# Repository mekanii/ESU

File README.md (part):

# 1. General Concept

# 2. Component
## 2.1. Monopolar Switch Detection (MSD)
### 2.1.1. Schematic

### 2.1.2. Output Scope
- Cut
- Coag

## 2.2. Return Electrode Monitor (REM)
### 2.2.1. Schematic

### 2.2.2. Output Scope
#### 2.2.2.1. Transformer
Below is the output scope at the input and output of toroidal transformer.

#### 2.2.2.2 Sense
> [!NOTE]
> All measurements for Return Electrode Monitoring do not utilize a physical Return Electrode; instead, a variable resistor is used. Therefore, all references to **pad resistance** in this context describe the variable resistor that simulates the Return Electrode.

Below is the output scope from the sense circuit, where the pad resistance values are 5Ω, 200Ω, 1kΩ, and High Impedance. The voltages measured by the oscilloscope are 10.385 mV, 558.91 mV, 689.31 mV, and 1.1164 V, respectively.

The ESP32's ADC provides a versatile and powerful way to read analog signals with a resolution of up to 12 bits and operates with a reference voltage of 0V to 3.3V (the default voltage range). Below is the formula to calculate the voltage per level for the ADC at 12-bit resolution.

$Voltage \ per \ Level = \frac{Voltage \ Range}{2^{Resolution}} = \frac{3.3V - 0V}{2^{12}} = \frac{3.3V}{4096} ≈ 0.00080586V ≈ 0.80586 mV$

Below is the formula to calculate the ADC value based on the voltage sense and the Voltage per Level.

$ADC \ Value = \frac{V_{sense}}{Voltage \ per \ Level}$

Using the formula above, we have the following ADC values for different pad resistances:

<div align="center">

| Pad Resistance | Measured Voltage | ADC Value |
| -------------: | ---------------: | --------: |
|             5Ω |        10.385 mV |        19 |
|           200Ω |        558.91 mV |       694 |
|            1kΩ |        689.31 mV |       855 |
|         High-Z |        1116.4 mV |      1385 |

</div>

## 2.3. Controller
### 2.3.1. PWM Generator
#### 2.3.1.1. Using the Remote Control Module (RMT) of ESP32 for Generating PWM Signals
The Remote Control Module (RMT) on the ESP32 is a versatile hardware peripheral designed primarily for sending and receiving infrared signals. However, it can also be effectively utilized to generate precise Pulse Width Modulation (PWM) signals.

#### 2.3.1.2. Key Concepts
- Duty Cycle:<br>The duty cycle of a PWM signal is the percentage of one cycle in which the signal is high (on) versus low (off). It is typically expressed as a value between 0 and 100.
- Total Period:<br>The total period of the PWM signal is the sum of the HIGH time and LOW time.

#### 2.3.1.3. Configuration
##### a. Clock Divider
The clock divider is a crucial parameter in microcontroller and digital circuit design that determines the frequency of a clock signal by dividing the input clock frequency, which is APB_CLK (80 MHz) for ESP32.

$Clock \ Divider = \frac{APB \_ CLK}{Clock \ Frequency}$

##### b. Resolution
The resolution in duty cycle is a crucial parameter in microcontroller and digital circuit design that determines the granularity of control over the PWM signal. It defines how finely the duty cycle can be adjusted, allowing for precise modulation of the output signal. In the case of the ESP32, the resolution is influenced by the clock frequency which ultimately affect the ability to achieve desired output levels.

$Resolution = \frac{Clock \ Frequency}{PWM \ Frequency}$

##### c. Combination of Clock Frequency and Resolution
The combination of clock frequency and resolution plays a vital role in determining the performance of PWM signals in microcontroller applications. The clock frequency sets the base rate at which the system operates, while the resolution defines how many discrete levels the duty cycle can be divided into. A higher clock frequency allows for faster switching and more precise timing, while a higher resolution enables finer control over the duty cycle. Together, they influence the accuracy and responsiveness of the PWM output, making it essential to balance these parameters to meet the specific requirements of the application.

<div align="center">

| Mode          | f PWM    | f Clock  | Clock Div | Resolution | 
| ------------- | -------: | -------: | --------: | ---------: |
| Pure Cut      |  400 kHz |   80 MHz |         1 |        200 |
| Blend Cut 1   |  400 kHz |   80 MHz |         1 |        200 |
| Blend Cut 2   |  400 kHz |   80 MHz |         1 |        200 |
| Coag Spray    |   25 kHz |   10 MHz |         8 |        800 |
| Coag Forced   |   20 kHz |   10 MHz |         8 |       1000 |
| Coag Standard |  400 kHz |   80 MHz |         1 |        200 |

</div>

#### 2.3.1.4. Output Scope
##### a. 400kHz
- Pattern 1
<br>The image illustrates the output scope for the Pattern 1 (Pure Cut operation) at the PWM generator. It provides a detailed view of the waveform characteristics and performance metrics associated with the Pure Cut process, highlighting the key features and behavior of the PWM signal during this operation.
<br>For discrete levels ranging from 10 to 100, demonstrates similar PWM frequency, indicating consistent performance across these duty cycle settings.

> [!NOTE]
> 400kHz PWM signal utilize a discrete resolution of 200 levels.

<!--  -->

- Pattern 2<br>
The image illustrates the output scope for the Pattern 2 (Blend Cut 1) operation at the PWM generator. It provides a detailed view of the waveform characteristics and performance metrics associated with the Blend Cut process, highlighting the key features and behavior of the PWM signal during this operation.<br>
For discrete levels ranging from 10 to 100, demonstrates similar PWM frequency and similar waveform HIGH state periods, indicating consistent performance across these duty cycle settings. Each pulse in Blend Cut 1 is similar to a single pulse of a Pattern 1 (Pure Cut) PWM signal.

> [!NOTE]
> Pattern 2: 18 pulses per 1 modulation (400 kHz for each pulse, with 0% PWM during the last 2 periods).<br>This pattern utilize a discrete resolution of 200 levels, similar to that of a Pattern 1 (Pure Cut) PWM signal.

- Pattern 3
<br>The image illustrates the output scope for the Pattern 3 (Blend Cut 2) operation at the PWM generator. It provides a detailed view of the waveform characteristics and performance metrics associated with the Blend Cut process, highlighting the key features and behavior of the PWM signal during this operation.
<br>For discrete levels ranging from 10 to 100, demonstrates similar PWM frequency and similar waveform HIGH state periods, indicating consistent performance across these duty cycle settings. Each pulse in Blend Cut 2 is similar to a single pulse of a Pure Cut PWM signal.

> [!NOTE]
> Pattern 3: 17 pulses per 1 modulation (400 kHz for each pulse, with 0% PWM during the last 3 periods).<br>This pattern utilize a discrete resolution of 200 levels, similar to that of a Pattern 1 (Pure Cut) PWM signal.

<!--  -->

##### b. 25kHz
The image illustrates the output scope for the 25kHz (Spray Coagulation operation) at the PWM generator. It provides a detailed view of the waveform characteristics and performance metrics associated with the Spray Coagulation process, highlighting the key features and behavior of the PWM signal during this operation.

For discrete levels ranging from 10 to 100, demonstrates similar PWM frequency, indicating consistent performance across these duty cycle settings. We can observe that the increment of the duty cycle results in a pulse that exhibits a linear increase in HIGH time, further emphasizing the effectiveness of the PWM modulation in maintaining a predictable response across varying duty cycle levels.

> [!NOTE]
> 25kHz PWM signal utilize a discrete resolution of 800 levels.

<p align="center">

</p>

<div align="center">

| Discrete Level  | Duty Cycle  | HIGH Time | LOW Time  |
| ---------------:| -----------:| ---------:| ---------:|
|              10 |      1.25 % |    0.5 µs |   39.5 µs |
|              20 |      2.50 % |    1.0 µs |   39.0 µs |
|              30 |      3.75 % |    1.5 µs |   38.5 µs |
|              40 |      5.00 % |    2.0 µs |   38.0 µs |
|              50 |      6.25 % |    2.5 µs |   37.5 µs |
|              60 |      7.50 % |    3.0 µs |   37.0 µs |
|              70 |      8.75 % |    3.5 µs |   36.5 µs |
|              80 |     10.00 % |    4.0 µs |   36.0 µs |
|              90 |     11.25 % |    4.5 µs |   35.5 µs |
|             100 |     12.50 % |    5.0 µs |   35.0 µs |

</div>

##### c. 20kHz
The image illustrates the output scope for the 20kHz (Forced Coagulation operation) at the PWM generator. It provides a detailed view of the waveform characteristics and performance metrics associated with the Forced Coagulation process, highlighting the key features and behavior of the PWM signal during this operation.

For discrete levels ranging from 10 to 100, demonstrates similar PWM frequency, indicating consistent performance across these duty cycle settings. We can observe that the increment of the duty cycle results in a pulse that exhibits a linear increase in HIGH time, further emphasizing the effectiveness of the PWM modulation in maintaining a predictable response across varying duty cycle levels.

> [!NOTE]
> 20kHz PWM signal utilize a discrete resolution of 1000 levels.

<p align="center">

</p>

<div align="center">

| Discrete Level  | Duty Cycle  | HIGH Time | LOW Time  |
| ---------------:| -----------:| ---------:| ---------:|
|              10 |      1.00 % |    0.5 µs |   49.5 µs |
|              20 |      2.00 % |    1.0 µs |   49.0 µs |
|              30 |      3.00 % |    1.5 µs |   48.5 µs |
|              40 |      4.00 % |    2.0 µs |   48.0 µs |
|              50 |      5.00 % |    2.5 µs |   47.5 µs |
|              60 |      6.00 % |    3.0 µs |   47.0 µs |
|              70 |      7.00 % |    3.5 µs |   46.5 µs |
|              80 |      8.00 % |    4.0 µs |   46.0 µs |
|              90 |      9.00 % |    4.5 µs |   45.5 µs |
|             100 |     10.00 % |    5.0 µs |   45.0 µs |

</div>

### 2.3.2. Communication Protocol
<!-- 0x5000-0x7FFF can be used as the variable address range; 0x8000-0xFFFF -->
The system UART mode is fixed to 8N1, and the baud rate is 115200.

**Frame Structure**

The data frame consists of 5 data blocks:

```[HEADER] [LENGTH] [INSTRUCTION] [PAYLOAD] [CRC]```

**Frame Components**

<table>
  <thead>
    <tr>
      <td>Block</td>
      <td>Size [byte]</td>
      <td>Description</td>
      <td>Value</td>
    </tr>
  </thead>
  <tbody>
    <tr>
      <td>HEADER</td>
      <td>2</td>
      <td>Frame start marker</td>
      <td>0x5A 0XA5</td>
    </tr>
    <tr>
      <td>LENGTH</td>
      <td>1</td>
      <td>Total bytes after HEADER</td>
      <td>INSTRUCTION + DATA + CRC</td>
    </tr>
    <tr>
      <td>INSTRUCTION</td>
      <td>1</td>
      <td>Instruction Code</td>
      <td>0x82 : Write<br>0x83 : Read</td>
    </tr>
    <tr>
      <td>PAYLOAD</td>
      <td>0 - 3</td>
      <td>Payload data</td>
      <td></td>
    </tr>
    <tr>
      <td>CRC</td>
      <td>2</td>
      <td>Cyclic Redundancy Check</td>
      <td></td>
    </tr>
  </tbody>
</table>

The `PAYLOAD` frame consist 3 data blocks:

```[VP ADDRESS] [NUMBER OF WORDS] [DATA]```

<table>
  <thead>
    <tr>
      <td>Block</td>
      <td>Size [byte]</td>
      <td>Description</td>
    </tr>
  </thead>
  <tbody>
    <tr>
      <td>VP ADDRESS</td>
      <td>2</td>
      <td>Variable Pointer address to read from</td>
    </tr>
    <tr>
      <td>NUMBER OF WORDS</td>
      <td>1</td>
      <td>Number of data words to read (always 1)</td>
    </tr>
    <tr>
      <td>DATA</td>
      <td>2</td>
      <td>Data word read from the specified VP address</td>
    </tr>
  </tbody>
</table>

#### 2.3.2.1. Basic System Operations

<table>
  <thead>
    <tr>
      <td nowrap>Command</td>
      <td nowrap>Variable</td>
      <td nowrap>VP ADDRESS</td>
      <td>INSTRUCTION</td>
      <td nowrap>Data Frame</td>
      <td nowrap>Response</td>
    </tr>
  </thead>
  <tbody>
    <tr></tr>
    <tr>
      <td nowrap>System status query</td>
      <td><pre>(byte) vp_50[0]</pre></td>
      <td><pre>50 00</pre></td>
      <td><pre>83</pre></td>
      <td><pre>5A A5 08 [INSTRUCTION] 50 00 01 [DATA:H DATA:L] CRC:L CRC:H</pre></td>
      <td nowrap></td>
    </tr>
    <tr></tr>
    <tr>
      <td nowrap>System reset</td>
      <td><pre>(byte) vp_50[1]</pre></td>
      <td><pre>50 01</pre></td>
      <td><pre>82</pre></td>
      <td><pre>5A A5 08 [INSTRUCTION] 50 01 01 [DATA:H DATA:L] CRC:L CRC:H</pre></td>
      <td nowrap></td>
    </tr>
    <tr></tr>
    <tr>
      <td nowrap>Stop all RMT transmission</td>
      <td><pre>(byte) vp_50[2]</pre></td>
      <td><pre>50 02</pre></td>
      <td><pre>82</pre></td>
      <td><pre>5A A5 08 [INSTRUCTION] 50 02 01 [DATA:H DATA:L] CRC:L CRC:H</pre></td>
      <td nowrap></td>
    </tr>
  </tbody>
</table>

#### 2.3.2.2. Mode Selection
<table>
  <thead>
    <tr>
      <td nowrap>Command</td>
      <td nowrap>Variable</td>
      <td nowrap>VP ADDRESS</td>
      <td>INSTRUCTION</td>
      <td nowrap>Data Frame</td>
      <td nowrap>DATA</td>
      <td nowrap>Response</td>
    </tr>
  </thead>
  <tbody>
    <tr></tr>
    <tr>
      <td nowrap>Get/set mode selection Cut</td>
      <td><pre>(int) vp_51[0]</pre></td>
      <td><pre>51 00</pre></td>
      <td><pre>82 | 83</pre></td>
      <td><pre>5A A5 08 [INSTRUCTION] 51 00 01 [DATA:H DATA:L] CRC:L CRC:H</pre></td>
      <td nowrap>
        <pre>0: 400kHz - Pattern 1
1: 400kHz - Pattern 2
2: 400kHz - Pattern 3</pre>
      </td>
      <td nowrap></td>
    </tr>
    <tr></tr>
    <tr>
      <td nowrap>Get/set mode selection Coag</td>
      <td><pre>(int) vp_51[1]</pre></td>
      <td><pre>51 01</pre></td>
      <td><pre>82 | 83</pre></td>
      <td><pre>5A A5 08 [INSTRUCTION] 51 01 01 [DATA:H DATA:L] CRC:L CRC:H</pre></td>
      <td nowrap>
        <pre>0: 25kHz
1: 20kHz
2: 400kHz - Bipolar Standard</pre>
      </td>
      <td nowrap></td>
    </tr>
  </tbody>
</table>

#### 2.3.2.2. Discrete Level Adjustment
<table>
  <thead>
    <tr>
      <td nowrap>Command</td>
      <td nowrap>Variable</td>
      <td nowrap>VP ADDRESS</td>
      <td>INSTRUCTION</td>
      <td nowrap>Data Frame</td>
      <td nowrap>DATA</td>
      <td nowrap>Response</td>
    </tr>
  </thead>
  <tbody>
    <tr></tr>
    <tr>
      <td nowrap>Get/set discrete level 400kHz - Pattern 1</td>
      <td><pre>(int) vp_52[0]</pre></td>
      <td><pre>52 00</pre></td>
      <td><pre>82 | 83</pre></td>
      <td><pre>5A A5 08 [INSTRUCTION] 52 00 01 [DATA:H DATA:L] CRC:L CRC:H</pre></td>
      <td nowrap><pre>0 - 200</pre></td>
      <td nowrap></td>
    </tr>
    <tr></tr>
    <tr>
      <td nowrap>Get/set discrete level 400kHz - Pattern 2</td>
      <td><pre>(int) vp_52[1]</pre></td>
      <td><pre>52 01</pre></td>
      <td><pre>82 | 83</pre></td>
      <td><pre>5A A5 08 [INSTRUCTION] 52 01 01 [DATA:H DATA:L] CRC:L CRC:H</pre></td>
      <td nowrap><pre>0 - 200</pre></td>
      <td nowrap></td>
    </tr>
    <tr></tr>
    <tr>
      <td nowrap>Get/set discrete level 400kHz - Pattern 3</td>
      <td><pre>(int) vp_52[3]</pre></td>
      <td><pre>52 02</pre></td>
      <td><pre>82 | 83</pre></td>
      <td><pre>5A A5 08 [INSTRUCTION] 52 03 01 [DATA:H DATA:L] CRC:L CRC:H</pre></td>
      <td nowrap><pre>0 - 200</pre></td>
      <td nowrap></td>
    </tr>
    <tr></tr>
    <tr>
      <td nowrap>Get/set discrete level 25kHz</td>
      <td><pre>(int) vp_53[0]</pre></td>
      <td><pre>53 00</pre></td>
      <td><pre>82 | 83</pre></td>
      <td><pre>5A A5 08 [INSTRUCTION] 53 00 01 [DATA:H DATA:L] CRC:L CRC:H</pre></td>
      <td nowrap><pre>0 - 800</pre></td>
      <td nowrap></td>
    </tr>
    <tr></tr>
    <tr>
      <td nowrap>Get/set discrete level 20kHz</td>
      <td><pre>(int) vp_53[1]</pre></td>
      <td><pre>53 01</pre></td>
      <td><pre>82 | 83</pre></td>
      <td><pre>5A A5 08 [INSTRUCTION] 53 01 01 [DATA:H DATA:L] CRC:L CRC:H</pre></td>
      <td nowrap><pre>0 - 1000</pre></td>
      <td nowrap></td>
    </tr>
    <tr></tr>
    <tr>
      <td nowrap>Get/set discrete level 400kHz - Bipolar Standard</td>
      <td><pre>(int) vp_54[0]</pre></td>
      <td><pre>54 00</pre></td>
      <td><pre>82 | 83</pre></td>
      <td><pre>5A A5 08 [INSTRUCTION] 54 00 01 [DATA:H DATA:L] CRC:L CRC:H</pre></td>
      <td nowrap><pre>0 - 200</pre></td>
      <td nowrap></td>
    </tr>
    
  </tbody>
</table>

## 2.4. Power Stage
### 2.4.1. HF Switch
#### 2.4.1.1. Schematic

#### 2.4.1.2. MOSFET Driver
We use the TC4420 as our MOSFET driver due to its high-speed performance and ability to efficiently drive N-channel MOSFETs in various applications. The TC4420 provides a peak output current of up to 6A, allowing for rapid charging and discharging of the MOSFET gate capacitance. This capability minimizes switching losses and enhances overall efficiency in power management.

Operating within a supply voltage range of 4.5V to 18V, the TC4420 can effectively drive MOSFET gates at a voltage level of 12V, ensuring that the MOSFET turns on fully for optimal performance. Its fast switching speed, with propagation delays in the nanosecond range (typically 55ns), is crucial for high-frequency applications, reducing transition times and heat generation.

#### 2.4.1.3. Utilizing Three IRFPE50 MOSFETs in Parallel for Enhanced Performance and Reliability
We use three IRFPE50 MOSFETs in parallel to enhance the overall performance and reliability of our circuit. The decision to parallel these MOSFETs is driven by several key factors:
- Increased Current Handling:<br>Each IRFPE50 MOSFET has a maximum continuous drain current rating of I<sub>D</sub>=7.8A at T<sub>C</sub>=25°C and I<sub>D</sub>=4.9A at T<sub>C</sub>=100°C. By connecting three times as many of them in parallel, we effectively triple the total current handling capability. This is particularly beneficial in applications where high current loads are expected, ensuring that the circuit can handle the demands without overheating or exceeding the MOSFET's ratings.
- Improved Thermal Management:<br>Paralleling MOSFETs helps distribute the heat generated during operation across multiple devices. This reduces the thermal stress on each individual MOSFET, allowing for better thermal management. Proper heat dissipation is crucial for maintaining performance and preventing thermal runaway, especially in high-power applications.
- Lower On-Resistance:<br>The IRFPE50 has a low on-resistance (R<sub>DS(on)</sub>) of approximately 1.2Ω. When MOSFETs are paralleled, the effective on-resistance decreases, which results in lower conduction losses. This is advantageous for improving the efficiency of the circuit, as it minimizes the voltage drop across the MOSFETs when they are in the on state.
- Redundancy and Reliability:<br>Using multiple MOSFETs in parallel provides a level of redundancy. If one MOSFET were to fail, the remaining devices can continue to operate, thereby enhancing the overall reliability of the circuit. This is particularly important in critical applications where failure could lead to significant issues.

#### 2.4.1.4. Output Scope
##### a. 400kHz
The image illustrates the output scope for the 400kHz operation at:
- MOSFET Driver Output (blue)
- MOSFET Drain Pin (yellow)
- VDS=72V

It provides a detailed view of the waveform characteristics and performance metrics associated with the Pure Cut process, highlighting the key features and behavior of the HF Switch signal during this operation.
<br>For discrete levels ranging from 20 to 180, demonstrates similar Waveform frequency, indicating consistent performance across these duty cycle settings.

> [!NOTE]
> 400kHz PWM signal utilize a discrete resolution of 200 levels.

<!--  -->

##### b. 25KHz

##### c. 25KHz

### 2.4.2. Transformer
**Toroidal Ferrite Core Transformer**

A toroidal ferrite core transformer is a type of transformer that uses a ring-shaped (toroidal) core made from ferrite material. Ferrite is a ceramic compound consisting of iron oxide mixed with other metals, which provides high magnetic permeability and low electrical conductivity. This makes ferrite ideal for high-frequency transformer applications.

**Structure and Construction**
- Core Shape<br>
  The core is a closed loop (doughnut-shaped), which helps confine the magnetic flux within the core material, minimizing leakage and electromagnetic interference (EMI).
- Windings<br>
  Copper wire is wound around the toroidal core, usually with primary and secondary windings placed concentrically. The windings can be distributed evenly around the core to further reduce leakage inductance and stray fields.
- Ferrite Material<br>
  Ferrite cores are preferred for high-frequency operation (tens of kHz to several MHz) because they have low core losses at these frequencies compared to laminated iron cores.

**Key Advantages**
- High Efficiency<br>
  The closed magnetic path of the toroid reduces core losses and leakage flux, resulting in higher efficiency.
- Low Electromagnetic Interference (EMI)<br>
  The toroidal shape confines the magnetic field, reducing EMI and making these transformers suitable for sensitive electronic circuits.
- Compact Size<br>
  For a given power rating, toroidal transformers are generally smaller and lighter than their laminated counterparts.
- Quiet Operation<br>
  The core shape and material minimize audible hum and vibration.

**Power Handling**

The transformer’s power rating is determined by the product of output voltage and current, and the core must be sized to avoid saturation at maximum load.

**Skin Effect**

At high frequencies, the skin effect is a phenomenon in alternating current (AC) where the current density becomes highest at the surface of a conductor and decreases exponentially toward the center. This occurs because the alternating current generates a changing magnetic field, which in turn induces **eddy currents** within the conductor. These eddy currents oppose the main current flow more strongly at the center, forcing most of the AC current to flow near the surface. As a result, the effective cross-sectional area available for current flow is reduced, increasing the effective resistance of the wire at higher frequencies.

The depth at which the current density falls to 37% of its value at the surface.

$δ = \sqrt{ \frac{ ρ } { π • f • μ } }$

Where:
- ρ = resistivity of the conductor (Ω·m)
- μ = permeability of the conductor (H/m)
- f = frequency (Hz)

For high-frequency windings, consider using multiple thinner wires in parallel (Litz wire) to reduce skin effect losses.

The calculated diameter above is based on DC or low-frequency AC. For high-frequency applications, the effective area may be less than the physical area due to skin effect.

#### 2.4.2.1. Design and Calculation
<!-- Given:
- Input voltage<br>$V_{in} = 72 \ V$
- Output voltage<br>$V_{out} = 216 \ V$
- Switching frequency<br>$f = 400 \ kHz = 400,000 \ Hz$
- Core dimensions:
  - Inner diameter<br>$ID = 23.3 \ mm$
  - Outer diameter<br>$OD = 40.4 \ mm$
  - Height<br>$H = 15.1 \ mm$
- Maximum flux density<br>$B_{max} = 350 \ Gauss$
- Output current<br>$I_{out} = 0.5 \ A$ -->

##### a. Core Cross-Sectional Area ($A_e$)
The effective cross-sectional area of the core is calculated as:

$A_e = \frac{( OD – ID ) • H }{ 2 }$

<!-- $A_e  = \frac{( 40.4 – 23.3 ) • 15.1 }{ 2 } = 129.1 \ mm^2$ -->

This area is important for determining how much magnetic flux the core can handle without saturating.

##### b. Primary Turns ($N_p$)
The number of primary turns is determined by:

$N_p = \frac{ V_{in} • Duty \ Cycle • 10^{10} }{ 2 • f • B_{max} • A_e }$

<!-- $N_p = \frac{ 72 • 0.5 • 10^{10} }{ 2 • 400,000 • 350 • 129.1 } = \frac{ 360,000,000,000 }{ 36,149,400,000 }$

$N_p = 9.96 ≈ 10 \ turns$ -->

This ensures the core does not saturate at the maximum input voltage and duty cycle.

##### c. Volt per Turn
The voltage induced per turn is:

$Volt \ per \ turn = \frac{ V_{in} }{ N_p }$

<!-- $Volt \ per \ turn = \frac{ 72 }{ 10 } = 7.2 \ V/turn$ -->

##### d. Secondary Turns ($N_s$)
The number of secondary turns is:

$N_s = \frac{ V_{out} }{ Volt \ per \ turn }$

<!-- $N_s = \frac{ 216 }{ 7.2 } = 30 \text{ turns}$ -->

This ensures the transformer provides the correct output voltage.

##### e. Output Power and Currents ($N_s$)
$P = V_{out} • I_{out}$

<!-- $P = 216 • 0.5 = 108 \ W$ -->

$I_{in} = \frac{ P }{ V_{in} }$

<!-- $I_{in} = \frac{ 108 }{ 72 } = 1.5 \ A$ -->

These calculations confirm the input current required to deliver the desired output power.

For high-frequency applications, we need to consider:
- **Skin effect** - Current tends to flow on the surface of conductors at high frequencies
- **Current density** - Typically 1.5-3 A/mm² for transformer applications
- **Temperature rise** - Higher current density = more heat

##### f. Wire Diameter
To calculate the required wire diameter for a given current, use the formula:<br><br>
$dW = \sqrt{ \frac{ 4 • I }{ \pi • J } }$

Where:
- $dW = wire \ diameter$
- $I = current \ (A)$
- $J = current \ density \ (A/mm^2)$

<!-- Primary:
- $I_{in} = 1.5 \ A$
- $Current \ Density = 1.5 \ A/mm^2$
- $dW_p = \sqrt{ \frac{ 4 • 1.5 }{ 3.14 • 1.5 } } = \sqrt{ \frac{ 6 }{ 4.712 } } = 1.13 \ mm$

Secondary:
- $I_{out} = 0.5 \ A$
- $Current \ Density = 1.5 \ A/mm^2$
- $dW_s = \sqrt{ \frac{ 4 • 0.5 }{ 3.14 • 1.5 } } = \sqrt{ \frac{ 2 }{ 4.712 } } = 0.65 \ mm$ -->

##### g. High-Frequency Considerations
The skin depth in copper is approximately calculated by following formula:

$δ = \sqrt{ \frac{ ρ } { π • f • μ } }$

If our calculated wire diameters are larger than 2× skin depth, consider using:
1. **Litz wire** for better high-frequency performance
2. **Multiple parallel smaller wires** instead of single thick wire with individual wire diameter 2x skin depth
3. **Stranded wire** with individual strand diameter 2x skin depth

##### h. Wire Specification for High-Frequency Operation using Stranded wire
Required copper area is the net copper cross‑section needed to carry the target current without exceeding your thermal/current‑density limit. Pick $J$ based on allowed temperature rise and cooling. Typical transformer design uses $J=1.5$–$3.0$ A/mm²; choose the lower end for continuous duty, compact windings, or poor airflow; higher values may be acceptable for pulsed or well‑cooled designs.

$A_{req} = \frac{I}{J}$

Area per strand is the metallic copper area of a single strand. Use the bare copper diameter (exclude enamel). If you only have an enamelled wire gauge, subtract twice the enamel thickness to estimate bare diameter, or use datasheet bare area.

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
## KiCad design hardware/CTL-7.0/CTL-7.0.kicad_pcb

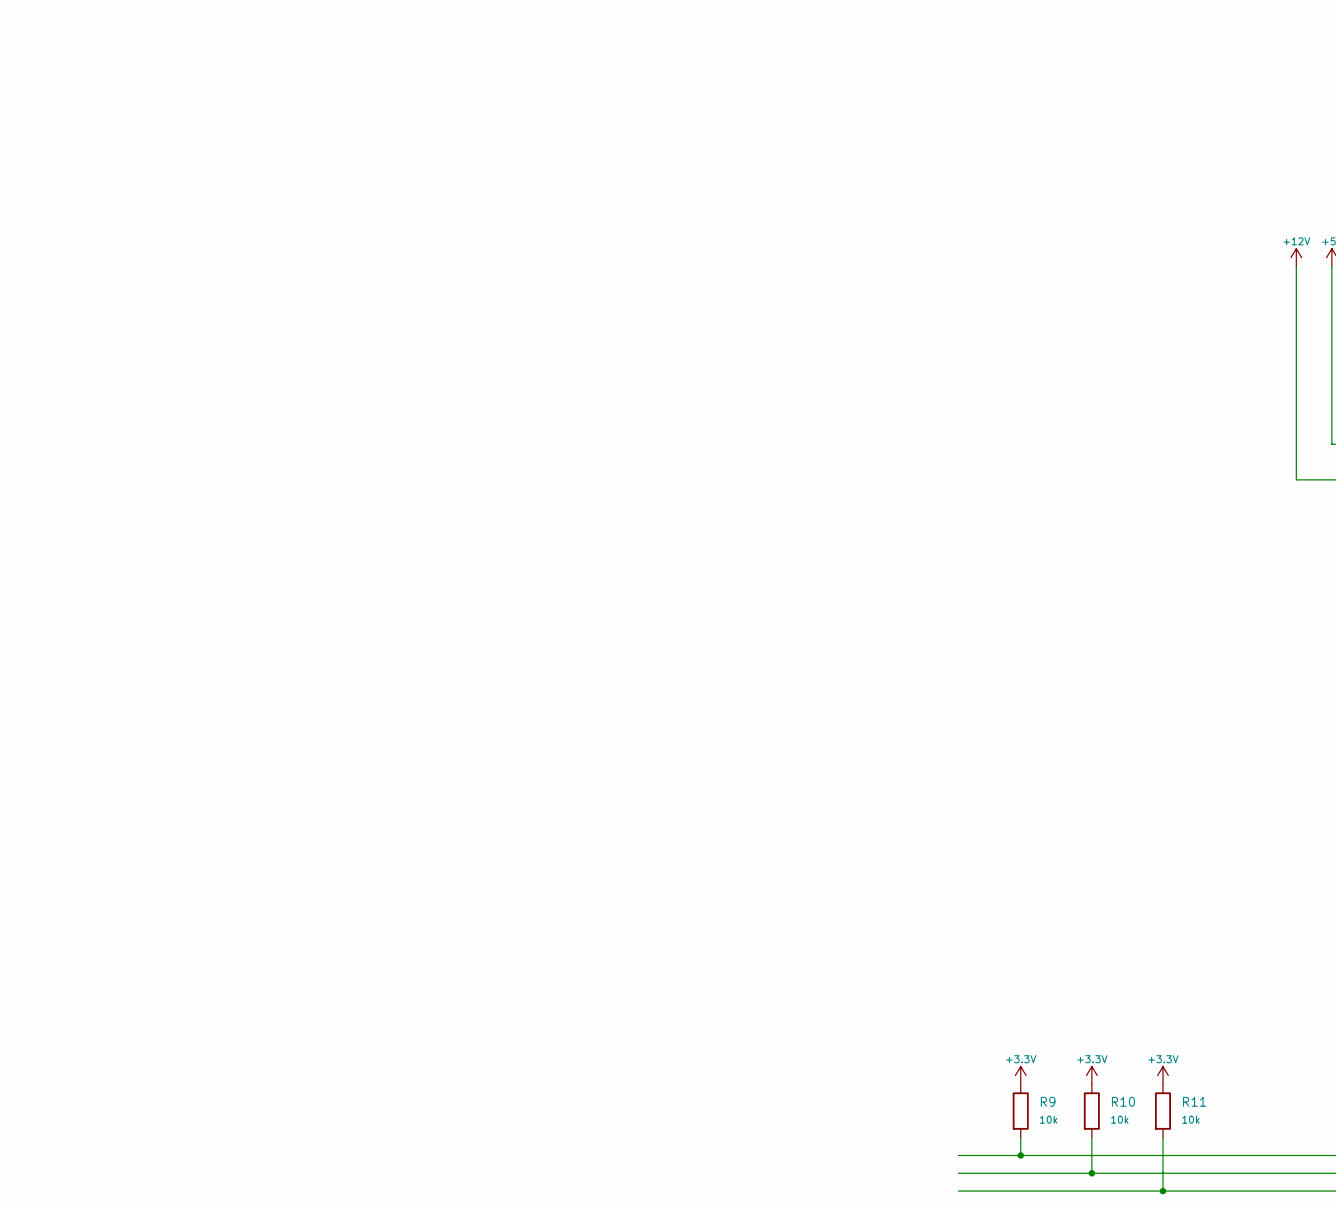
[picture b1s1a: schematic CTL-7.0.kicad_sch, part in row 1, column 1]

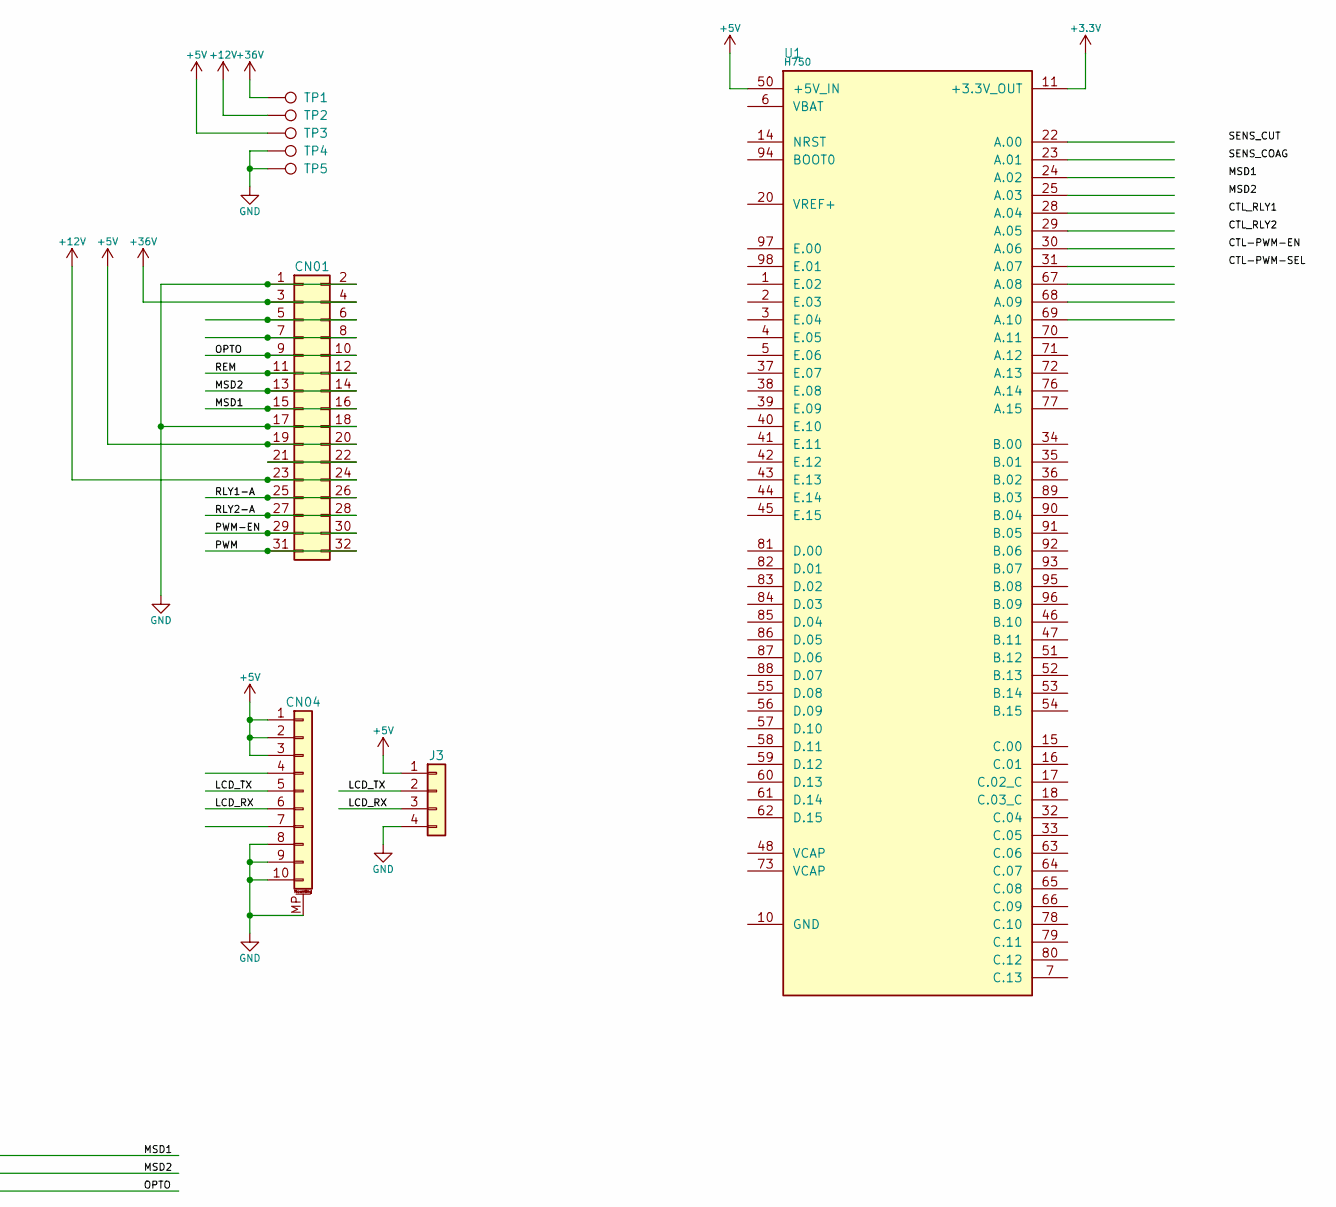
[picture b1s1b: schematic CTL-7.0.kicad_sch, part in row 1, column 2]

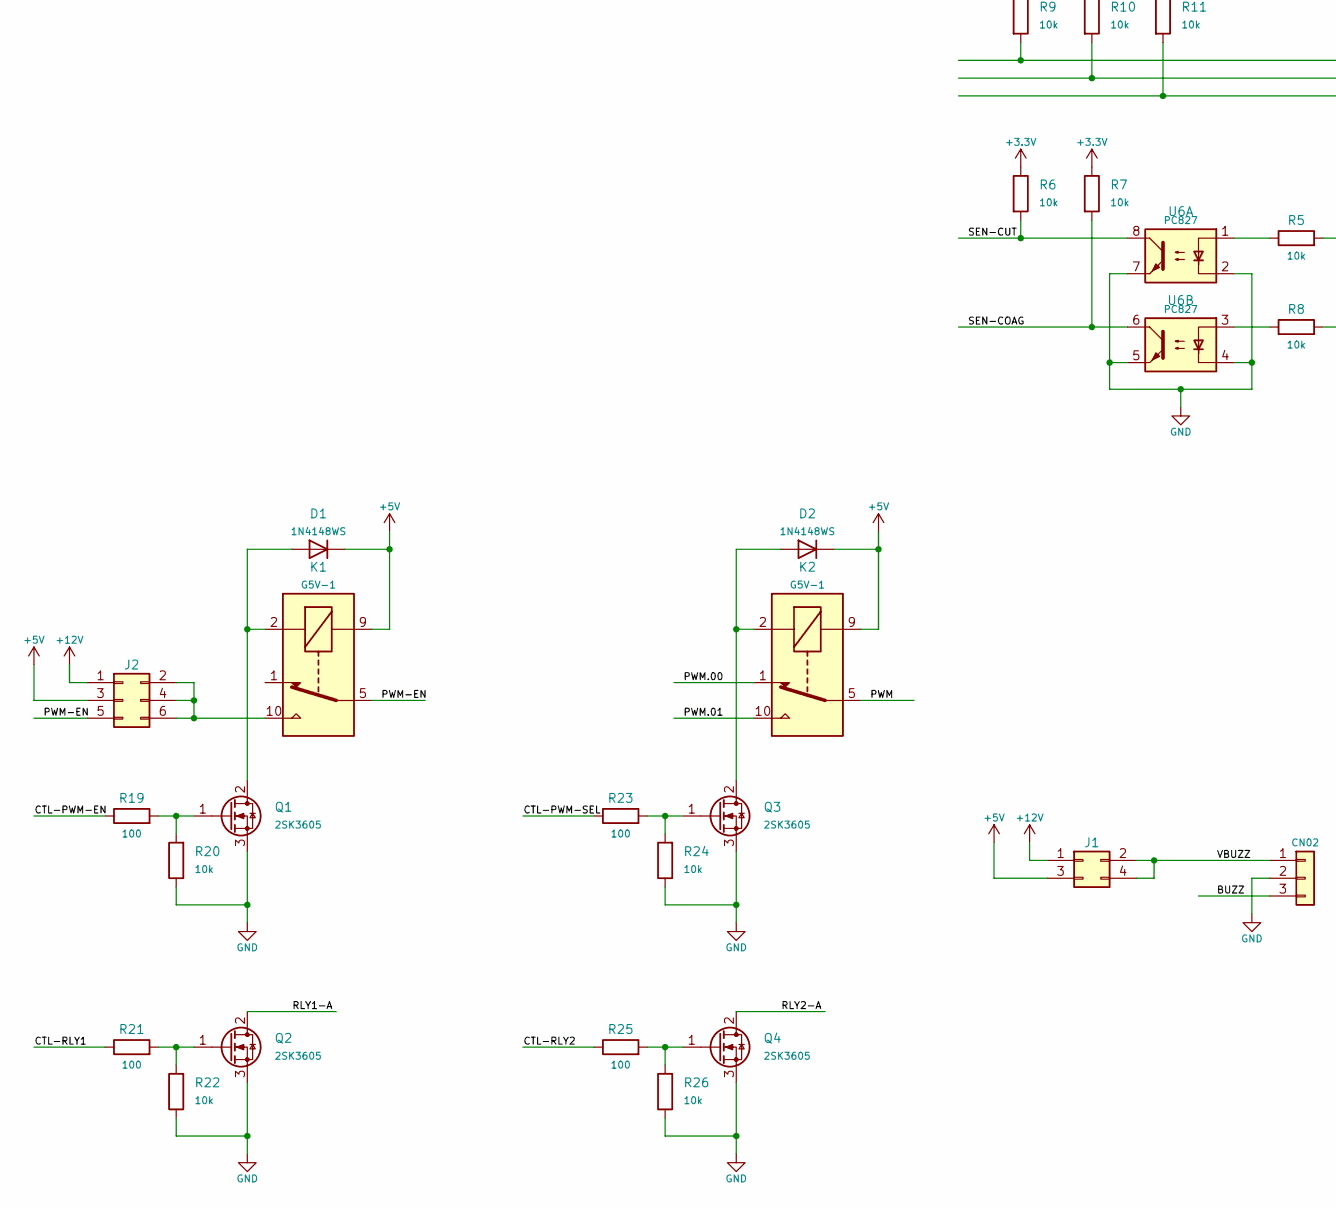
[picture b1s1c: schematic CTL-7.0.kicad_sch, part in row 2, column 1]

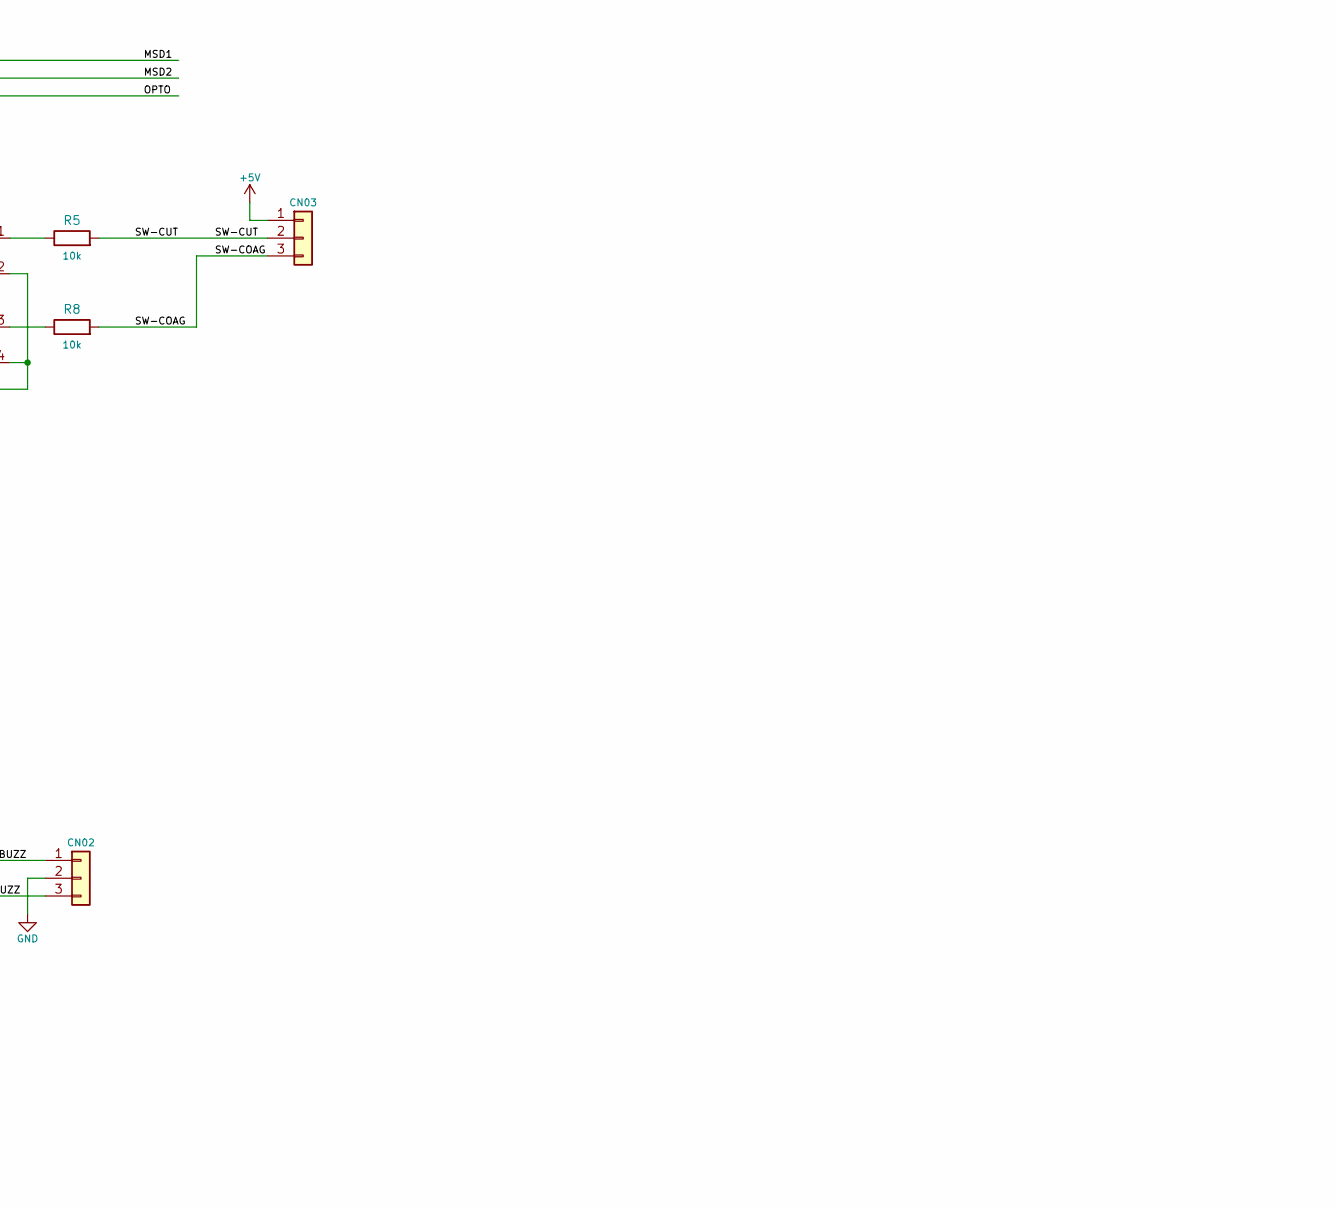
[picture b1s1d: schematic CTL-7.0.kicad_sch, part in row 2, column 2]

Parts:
CN01: Conn_02x16_Odd_Even; PinHeader_2x16_P2.54mm_Vertical
CN02, CN03: Conn_01x03; JST_XH_B3B-XH-A_1x03_P2.50mm_Vertical
CN04: TE_1-84952-0_1x10-1MP_P1.0mm_Horizontal
D1, D2: 1N4148WS; D_SOD-323
J1: Conn_02x02_Odd_Even; PinHeader_2x02_P2.54mm_Vertical_SMD
J2: Conn_02x03_Odd_Even; PinHeader_2x03_P2.54mm_Vertical_SMD
J3: Conn_01x04; PinHeader_1x04_P2.54mm_Vertical
K1, K2: G5V-1; Relay_SPDT_Omron_G5V-1
Q1, Q2, Q3, Q4: 2SK3605; SOT-89-3
R5, R6, R7, R8, R9, R10, R11, R20, R22, R24, R26: 10k; R_0805_2012Metric
R19, R21, R23, R25: 100; R_0805_2012Metric
TP1, TP2, TP3, TP4, TP5: TestPoint; TestPoint_THTPad_2.2225x2.2225mm_Drill1.5mm
U1: H750; STM32H750_v1
U6: PC827; DIP-8_W7.62mm_Socket

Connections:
+3.3V: R6.1, R7.1, R9.1, R10.1, R11.1, U1.11 (+3.3V_OUT), U1.27 (+3.3V_OUT), U1.75 (+3.3V_OUT), U1.100 (+3.3V_OUT)
+5V: CN01.19, CN01.20, CN03.1, CN04.1, CN04.2, CN04.3, D1.1 (K), D2.1 (K), J1.3, J2.3, J3.1, K1.9, K2.9, TP3.1 (1_1), U1.50 (+5V_IN)
+12V: CN01.23, CN01.24, J1.1, J2.1, TP2.1 (1_1)
+36V: CN01.3, CN01.4, TP1.1 (1_1)
/BUZZ: CN02.3
/CTL-PWM-EN: R19.1
/CTL-PWM-SEL: R23.1
/CTL-RLY1: R21.1
/CTL-RLY2: R25.1
/LCD_RX: CN04.6, J3.3
/LCD_TX: CN04.5, J3.2
/MSD1: CN01.15, CN01.16, R9.2
/MSD2: CN01.13, CN01.14, R10.2
/OPTO: CN01.9, CN01.10, R11.2
/PWM: CN01.31, CN01.32, K2.5, K2.6
/PWM-EN: CN01.29, CN01.30, J2.5, K1.5, K1.6
/PWM.00: K2.1
/PWM.01: K2.10
/REM: CN01.11, CN01.12
/RLY1-A: CN01.25, CN01.26, Q2.2 (D)
/RLY2-A: CN01.27, CN01.28, Q4.2 (D)
/SEN-COAG: R7.2, U6.6
/SEN-CUT: R6.2, U6.8
/SW-COAG: CN03.3, R8.2
/SW-CUT: CN03.2, R5.2
/VBUZZ: CN02.1, J1.2, J1.4
unnamed: CN01.5, CN01.6
unnamed: CN01.7, CN01.8
unnamed: CN01.21, CN01.22
unnamed: D1.2 (A), K1.2, Q1.2 (D)
unnamed: D2.2 (A), K2.2, Q3.2 (D)
unnamed: J2.2, J2.4, J2.6, K1.10
unnamed: Q1.1 (G), R19.2, R20.2
unnamed: Q2.1 (G), R21.2, R22.2
unnamed: Q3.1 (G), R23.2, R24.2
unnamed: Q4.1 (G), R25.2, R26.2
unnamed: R5.1, U6.1
unnamed: R8.1, U6.3

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
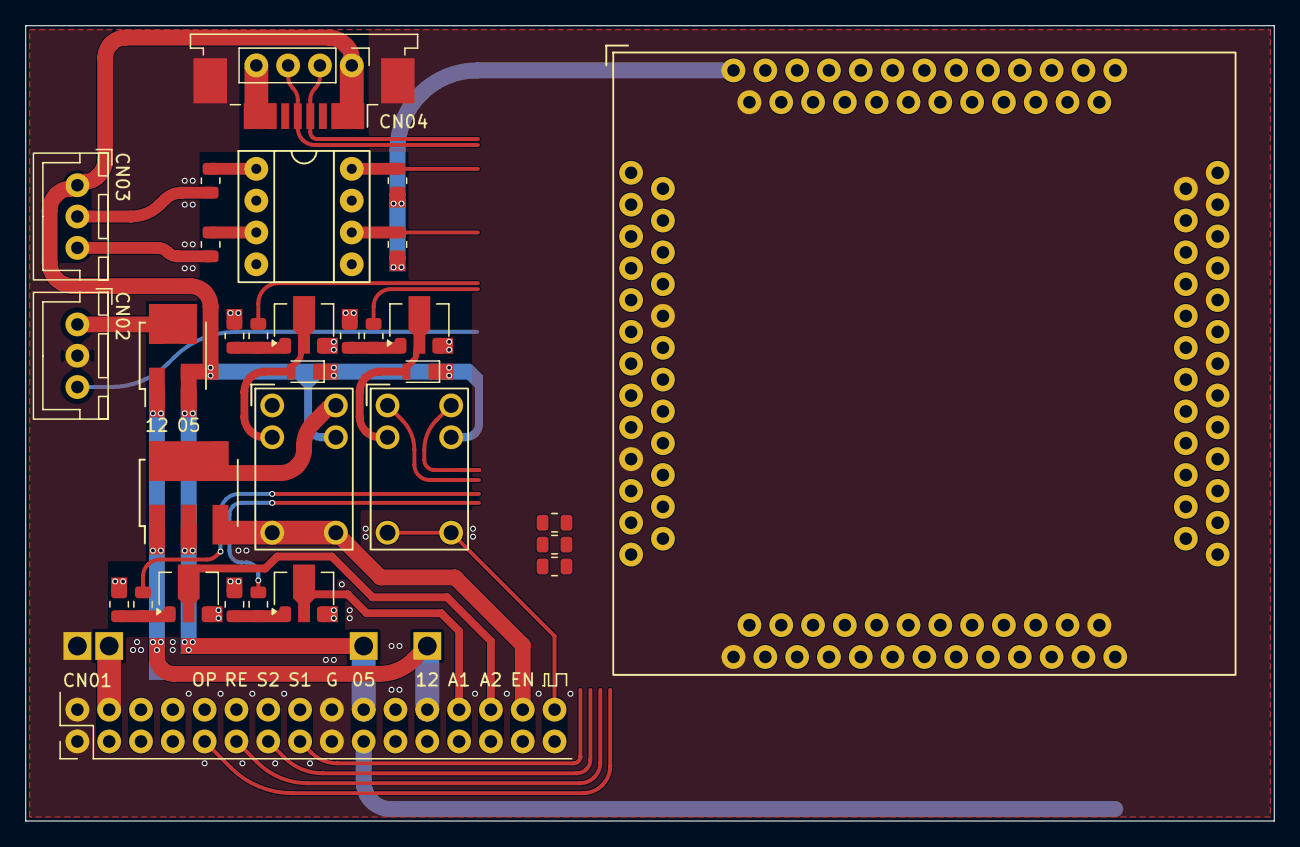
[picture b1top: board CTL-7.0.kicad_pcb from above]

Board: 2 copper layers, 99.7 x 63.5 mm, 36 parts (0 on the bottom side), 32 nets.

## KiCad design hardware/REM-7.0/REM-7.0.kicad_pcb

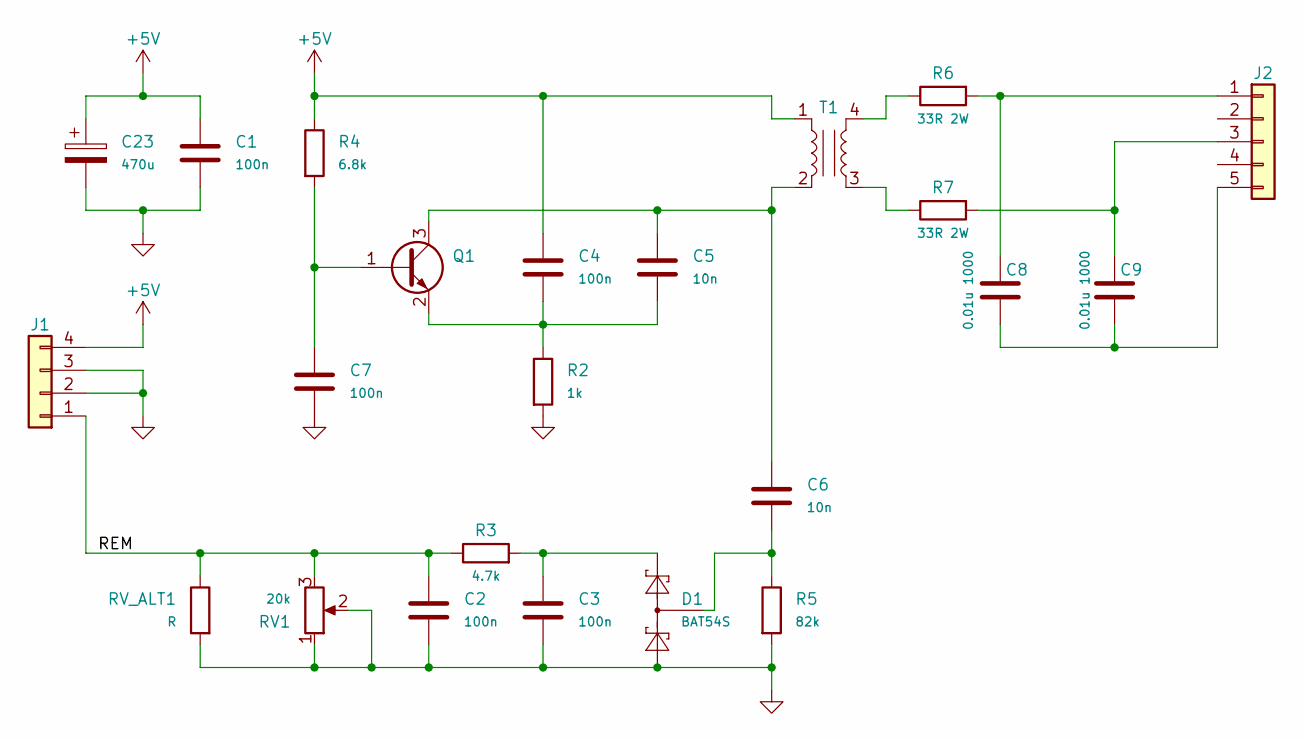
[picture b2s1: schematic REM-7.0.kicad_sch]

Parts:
C1, C2, C3, C4, C7: 100n; C_0805_2012Metric_Pad1.18x1.45mm_HandSolder
C5, C6: 10n; C_0805_2012Metric_Pad1.18x1.45mm_HandSolder
C8, C9: 0.01u 1000; C_Rect_L13.0mm_W5.0mm_P10.00mm_FKS3_FKP3_MKS4
C23: 470u; CP_EIA-7343-15_Kemet-W_HandSolder
D1: BAT54S; SOT-23
J1: Conn_01x04; PinHeader_1x04_P2.54mm_Horizontal
J2: Conn_01x05; PinHeader_1x05_P2.54mm_Horizontal
Q1: MMBT3904; SOT-23
R2: 1k; R_0805_2012Metric_Pad1.20x1.40mm_HandSolder
R3: 4.7k; R_0805_2012Metric_Pad1.20x1.40mm_HandSolder
R4: 6.8k; R_0805_2012Metric_Pad1.20x1.40mm_HandSolder
R5: 82k; R_0805_2012Metric_Pad1.20x1.40mm_HandSolder
R6, R7: 33R 2W; R_Axial_DIN0414_L11.9mm_D4.5mm_P20.32mm_Horizontal
RV1: 20k; Potentiometer_Bourns_3296W_Vertical
RV_ALT1: R; R_0805_2012Metric_Pad1.20x1.40mm_HandSolder
T1: Transformer_1P_1S; Transformer_EP13_1423

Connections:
+5V: C1.1, C4.1, C23.1, J1.4, R4.1, T1.1 (AA)
/REM: C2.1, J1.1, R3.1, RV1.3, RV_ALT1.1
GND: C1.2, C2.2, C3.2, C7.2, C23.2, D1.1 (A), J1.2, J1.3, R2.2, R5.2, RV1.1, RV1.2, RV_ALT1.2
unnamed: C6.2, D1.3 (COM), R5.1
unnamed: C3.1, D1.2 (K), R3.2
unnamed: C8.1, J2.1, R6.2
unnamed: C9.1, J2.3, R7.2
unnamed: C8.2, C9.2, J2.5
unnamed: C7.1, Q1.1 (B), R4.2
unnamed: C5.1, C6.1, Q1.3 (C), T1.2 (AB)
unnamed: C4.2, C5.2, Q1.2 (E), R2.1
unnamed: R7.1, T1.3 (SA)
unnamed: R6.1, T1.4 (SB)

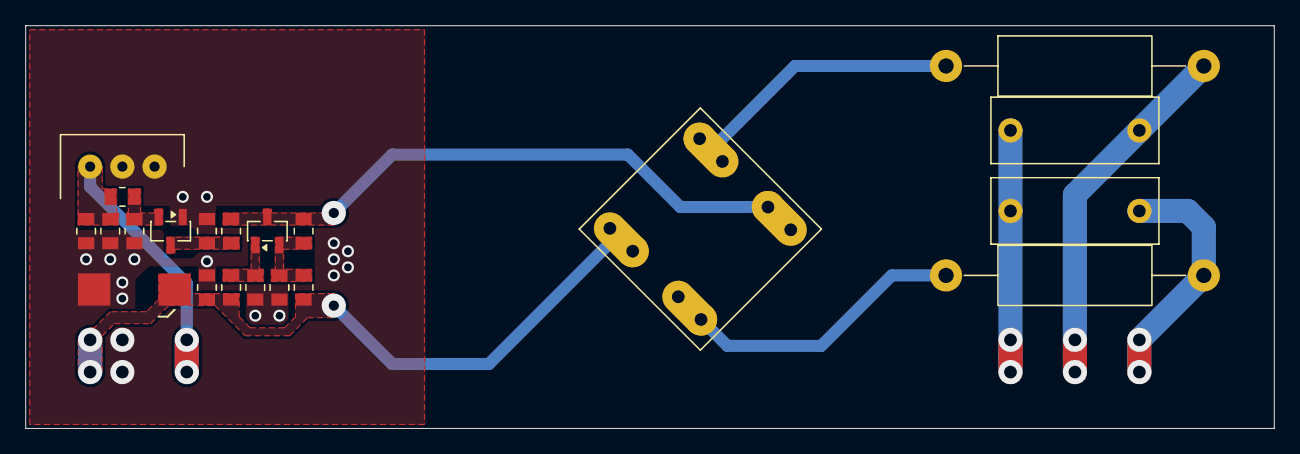
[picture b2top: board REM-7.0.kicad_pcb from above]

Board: 2 copper layers, 98.4 x 31.8 mm, 21 parts (0 on the bottom side), 13 nets.

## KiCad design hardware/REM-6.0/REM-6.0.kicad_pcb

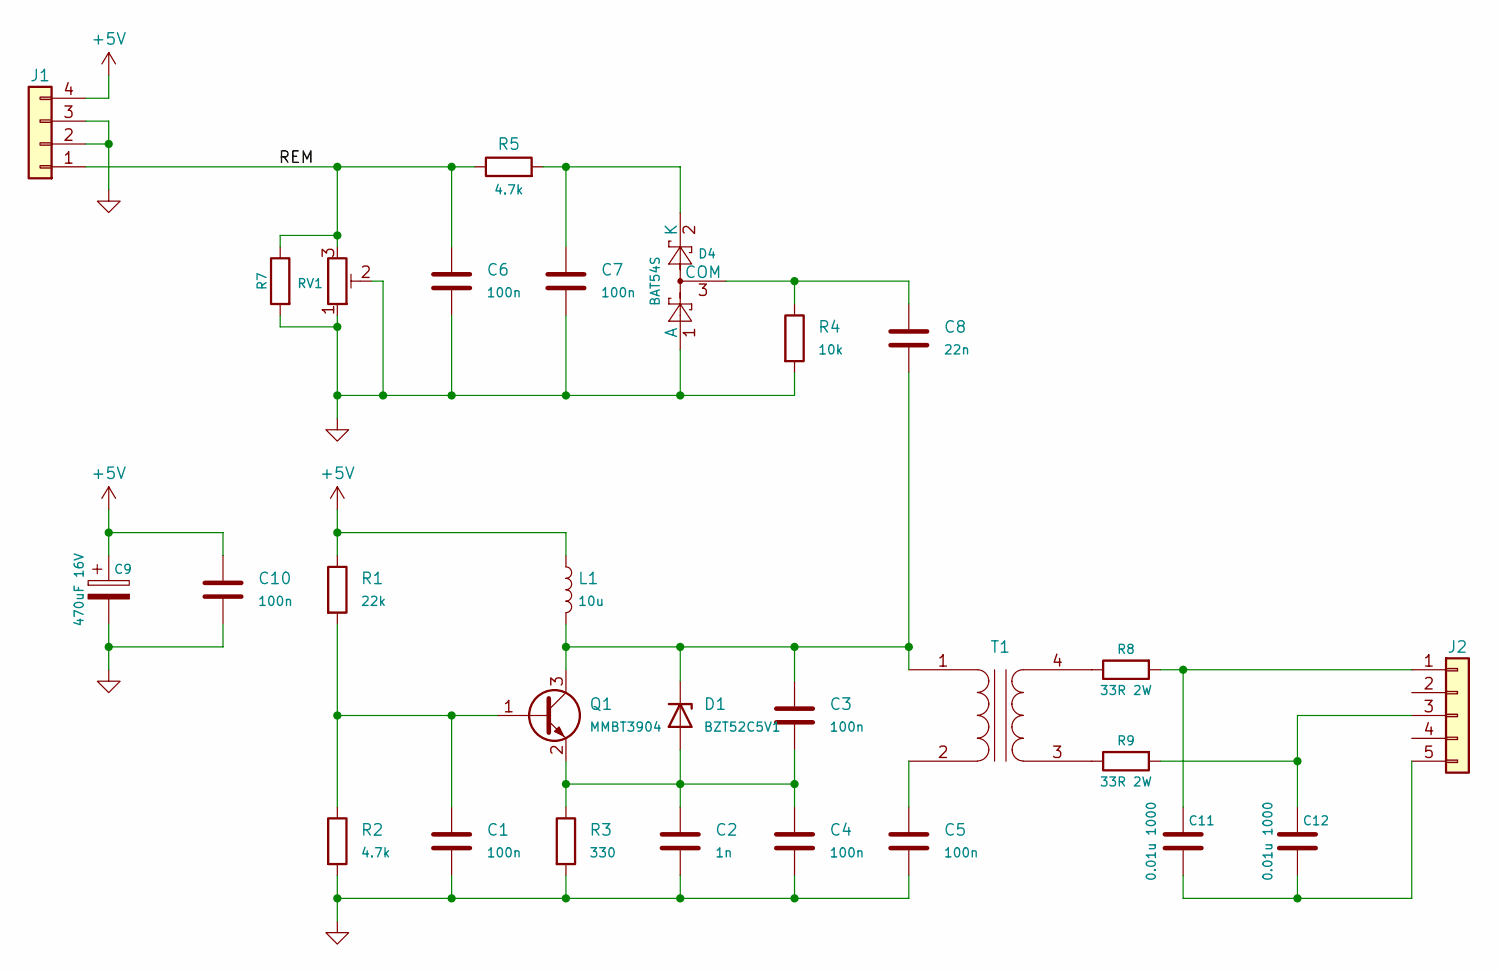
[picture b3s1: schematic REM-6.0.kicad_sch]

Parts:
C1, C3, C4, C5, C6, C7, C10: 100n; C_0805_2012Metric_Pad1.18x1.45mm_HandSolder
C2: 1n; C_0805_2012Metric_Pad1.18x1.45mm_HandSolder
C8: 22n; C_0805_2012Metric_Pad1.18x1.45mm_HandSolder
C9: 470uF 16V; CP_EIA-7343-15_Kemet-W_HandSolder
C11, C12: 0.01u 1000; C_Rect_L13.0mm_W5.0mm_P10.00mm_FKS3_FKP3_MKS4
D1: BZT52C5V1; D_SOD-123
D4: BAT54S; SOT-23
J1: PinHeader_2.54mm 02x04 Horizontal; PinHeader_1x04_P2.54mm_Horizontal
J2: Conn_01x05; PinHeader_1x05_P2.54mm_Horizontal
L1: 10u; L_10.4x10.4_H4.8
Q1: MMBT3904; SOT-23
R1: 22k; R_0805_2012Metric_Pad1.20x1.40mm_HandSolder
R2, R5: 4.7k; R_0805_2012Metric_Pad1.20x1.40mm_HandSolder
R3: 330; R_0805_2012Metric_Pad1.20x1.40mm_HandSolder
R4: 10k; R_0805_2012Metric_Pad1.20x1.40mm_HandSolder
R7: R_0805_2012Metric_Pad1.20x1.40mm_HandSolder
R8, R9: 33R 2W; R_Axial_DIN0414_L11.9mm_D4.5mm_P20.32mm_Horizontal
RV1: 5kΩ; Potentiometer_Bourns_3296W_Vertical
T1: Transformer_1P_1S; Transformer_Toroid_Horizontal_OD23.5mm_ID13.5mm

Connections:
+5V: C9.1, C10.1, J1.4, L1.1, R1.1
/REM: C6.1, J1.1, R5.1, R7.1, RV1.3
GND: C1.2, C2.2, C4.2, C5.2, C6.2, C7.2, C9.2, C10.2, D4.1 (A), J1.2, J1.3, R2.2, R3.2, R4.2, R7.2, RV1.1, RV1.2
unnamed: C2.1, C3.2, C4.1, D1.2 (A), Q1.2 (E), R3.1
unnamed: C3.1, C8.2, D1.1 (K), L1.2, Q1.3 (C), T1.1 (AA)
unnamed: C8.1, D4.3 (COM), R4.1
unnamed: C7.1, D4.2 (K), R5.2
unnamed: C11.1, J2.1, R8.2
unnamed: C12.1, J2.3, R9.2
unnamed: C11.2, C12.2, J2.5
unnamed: C1.1, Q1.1 (B), R1.2, R2.1
unnamed: C5.1, T1.2 (AB)
unnamed: R9.1, T1.3 (SA)
unnamed: R8.1, T1.4 (SB)

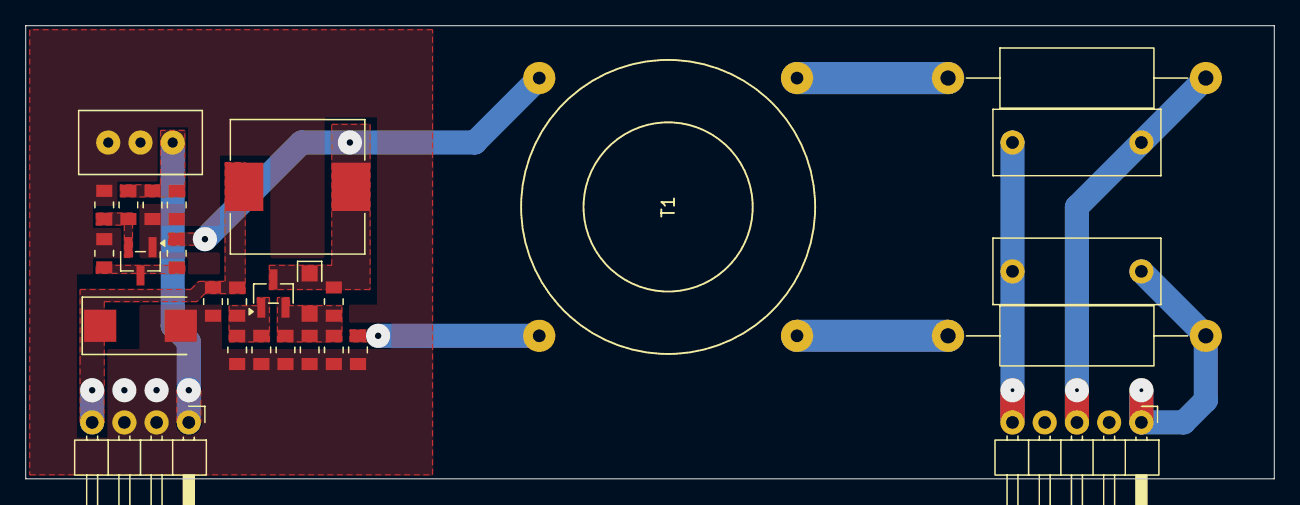
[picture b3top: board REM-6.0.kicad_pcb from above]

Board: 2 copper layers, 98.4 x 35.7 mm, 28 parts (0 on the bottom side), 14 nets.
